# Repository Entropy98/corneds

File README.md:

# Dependencies
 * PyOCD
 * Pico-SDK
 * gdb-multiarch
 * gcc-arm-none-eabi

# Flashing
1. run `./scripts/flash.sh ./build/corneds_<side>.elf` in the firmware directory
2. Enter `target remote localhost:3333` to connect to started gdb server
**cannot connect with gdb-multiarch --pid argument due to ptrace vulnerability in system**

# To Do
## PCB

## Hardware

## Firmware
 * Tests
   * test debug_print test
     * unclear why uart isn't working

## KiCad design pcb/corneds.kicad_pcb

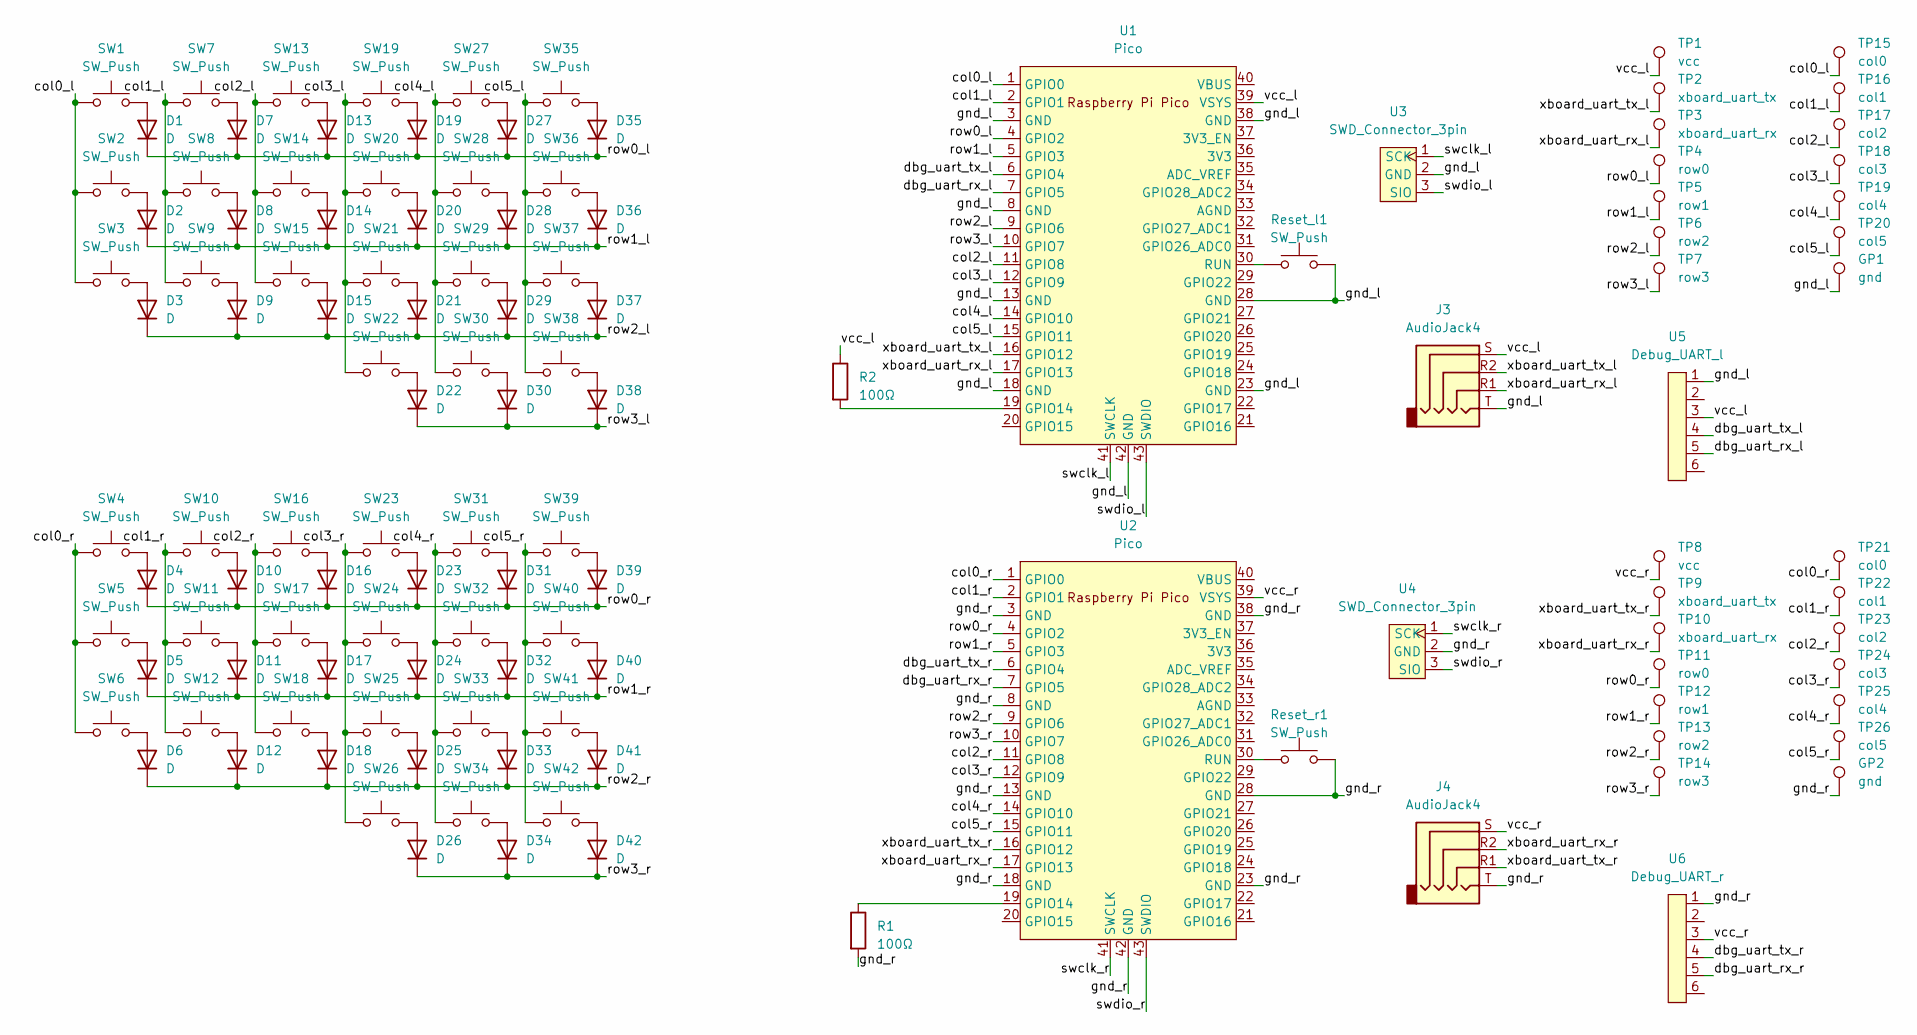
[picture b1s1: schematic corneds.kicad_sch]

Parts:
D1, D2, D3, D4, D5, D6, D7, D8, D9, D10, D11, D12, D13, D14, D15, D16, D17, D18, D19, D20, D21, D22, D23, D24, D25, D26, D27, D28, D29, D30, D31, D32, D33, D34, D35, D36, D37, D38, D39, D40, D41, D42: D; D_1206_3216Metric
GP1, GP2: gnd; PinHeader_1x01_P2.54mm_Vertical
J3, J4: AudioJack4; Jack_3.5mm_boardsource_TRRS_TH
R1, R2: 100Ω; R_0603_1608Metric
Reset_l1: SW_Push; SW_PTS636_SK25F_SMTR
Reset_r1: SW_Push; SW_PTS636_SK25F_SMTR
SW1, SW2, SW3, SW4, SW5, SW6, SW7, SW8, SW9, SW10, SW11, SW12, SW13, SW14, SW15, SW16, SW17, SW18, SW19, SW20, SW21, SW22, SW23, SW24, SW25, SW26, SW27, SW28, SW29, SW30, SW31, SW32, SW33, SW34, SW35, SW36, SW37, SW38, SW39, SW40, SW41, SW42: SW_Push; Kailh_socket_MX
TP1, TP8: vcc; PinHeader_1x01_P2.54mm_Vertical
TP2, TP9: xboard_uart_tx; PinHeader_1x01_P2.54mm_Vertical
TP3, TP10: xboard_uart_rx; PinHeader_1x01_P2.54mm_Vertical
TP4, TP11: row0; PinHeader_1x01_P2.54mm_Vertical
TP5, TP12: row1; PinHeader_1x01_P2.54mm_Vertical
TP6, TP13: row2; PinHeader_1x01_P2.54mm_Vertical
TP7, TP14: row3; PinHeader_1x01_P2.54mm_Vertical
TP15, TP21: col0; PinHeader_1x01_P2.54mm_Vertical
TP16, TP22: col1; PinHeader_1x01_P2.54mm_Vertical
TP17, TP23: col2; PinHeader_1x01_P2.54mm_Vertical
TP18, TP24: col3; PinHeader_1x01_P2.54mm_Vertical
TP19, TP25: col4; PinHeader_1x01_P2.54mm_Vertical
TP20, TP26: col5; PinHeader_1x01_P2.54mm_Vertical
U1, U2: Pico; RPi_Pico_SMD_TH
U3, U4: SWD_Connector_3pin; SM03B-SRSS-TB
U5: Debug_UART_l; Header_6pin
U6: Debug_UART_r; Header_6pin

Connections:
/col0_l: SW1.1, SW2.1, SW3.1, TP15.1, U1.1 (GPIO0)
/col0_r: SW4.1, SW5.1, SW6.1, TP21.1, U2.1 (GPIO0)
/col1_l: SW7.1, SW8.1, SW9.1, TP16.1, U1.2 (GPIO1)
/col1_r: SW10.1, SW11.1, SW12.1, TP22.1, U2.2 (GPIO1)
/col2_l: SW13.1, SW14.1, SW15.1, TP17.1, U1.11 (GPIO8)
/col2_r: SW16.1, SW17.1, SW18.1, TP23.1, U2.11 (GPIO8)
/col3_l: SW19.1, SW20.1, SW21.1, SW22.1, TP18.1, U1.12 (GPIO9)
/col3_r: SW23.1, SW24.1, SW25.1, SW26.1, TP24.1, U2.12 (GPIO9)
/col4_l: SW27.1, SW28.1, SW29.1, SW30.1, TP19.1, U1.14 (GPIO10)
/col4_r: SW31.1, SW32.1, SW33.1, SW34.1, TP25.1, U2.14 (GPIO10)
/col5_l: SW35.1, SW36.1, SW37.1, SW38.1, TP20.1, U1.15 (GPIO11)
/col5_r: SW39.1, SW40.1, SW41.1, SW42.1, TP26.1, U2.15 (GPIO11)
/dbg_uart_rx_l: U1.7 (GPIO5), U5.5
/dbg_uart_rx_r: U2.7 (GPIO5), U6.5
/dbg_uart_tx_l: U1.6 (GPIO4), U5.4
/dbg_uart_tx_r: U2.6 (GPIO4), U6.4
/gnd_l: GP1.1, J3.T, Reset_l1.2, U1.3 (GND), U1.8 (GND), U1.13 (GND), U1.18 (GND), U1.23 (GND), U1.28 (GND), U1.38 (GND), U1.42 (GND), U3.2 (GND), U5.1
/gnd_r: GP2.1, J4.T, R1.2, Reset_r1.2, U2.3 (GND), U2.8 (GND), U2.13 (GND), U2.18 (GND), U2.23 (GND), U2.28 (GND), U2.38 (GND), U2.42 (GND), U4.2 (GND), U6.1
/row0_l: D1.1 (K), D7.1 (K), D13.1 (K), D19.1 (K), D27.1 (K), D35.1 (K), TP4.1, U1.4 (GPIO2)
/row0_r: D4.1 (K), D10.1 (K), D16.1 (K), D23.1 (K), D31.1 (K), D39.1 (K), TP11.1, U2.4 (GPIO2)
/row1_l: D2.1 (K), D8.1 (K), D14.1 (K), D20.1 (K), D28.1 (K), D36.1 (K), TP5.1, U1.5 (GPIO3)
/row1_r: D5.1 (K), D11.1 (K), D17.1 (K), D24.1 (K), D32.1 (K), D40.1 (K), TP12.1, U2.5 (GPIO3)
/row2_l: D3.1 (K), D9.1 (K), D15.1 (K), D21.1 (K), D29.1 (K), D37.1 (K), TP6.1, U1.9 (GPIO6)
/row2_r: D6.1 (K), D12.1 (K), D18.1 (K), D25.1 (K), D33.1 (K), D41.1 (K), TP13.1, U2.9 (GPIO6)
/row3_l: D22.1 (K), D30.1 (K), D38.1 (K), TP7.1, U1.10 (GPIO7)
/row3_r: D26.1 (K), D34.1 (K), D42.1 (K), TP14.1, U2.10 (GPIO7)
/swclk_l: U1.41 (SWCLK), U3.1 (SCK)
/swclk_r: U2.41 (SWCLK), U4.1 (SCK)
/swdio_l: U1.43 (SWDIO), U3.3 (SIO)
/swdio_r: U2.43 (SWDIO), U4.3 (SIO)
/vcc_l: J3.S, R2.1, TP1.1, U1.39 (VSYS), U5.3
/vcc_r: J4.S, TP8.1, U2.39 (VSYS), U6.3
/xboard_uart_rx_l: J3.R1, TP3.1, U1.17 (GPIO13)
/xboard_uart_rx_r: J4.R2, TP10.1, U2.17 (GPIO13)
/xboard_uart_tx_l: J3.R2, TP2.1, U1.16 (GPIO12)
/xboard_uart_tx_r: J4.R1, TP9.1, U2.16 (GPIO12)
unnamed: D1.2 (A), SW1.2
unnamed: D2.2 (A), SW2.2
unnamed: D3.2 (A), SW3.2
unnamed: D4.2 (A), SW4.2
unnamed: D5.2 (A), SW5.2
unnamed: D6.2 (A), SW6.2
unnamed: D7.2 (A), SW7.2
unnamed: D8.2 (A), SW8.2
unnamed: D9.2 (A), SW9.2
unnamed: D10.2 (A), SW10.2
unnamed: D11.2 (A), SW11.2
unnamed: D12.2 (A), SW12.2
unnamed: D13.2 (A), SW13.2
unnamed: D14.2 (A), SW14.2
unnamed: D15.2 (A), SW15.2
unnamed: D16.2 (A), SW16.2
unnamed: D17.2 (A), SW17.2
unnamed: D18.2 (A), SW18.2
unnamed: D19.2 (A), SW19.2
unnamed: D20.2 (A), SW20.2
unnamed: D21.2 (A), SW21.2
unnamed: D22.2 (A), SW22.2
unnamed: D23.2 (A), SW23.2
unnamed: D24.2 (A), SW24.2
unnamed: D25.2 (A), SW25.2
unnamed: D26.2 (A), SW26.2
unnamed: D27.2 (A), SW27.2
unnamed: D28.2 (A), SW28.2
unnamed: D29.2 (A), SW29.2
unnamed: D30.2 (A), SW30.2
unnamed: D31.2 (A), SW31.2
unnamed: D32.2 (A), SW32.2
unnamed: D33.2 (A), SW33.2
unnamed: D34.2 (A), SW34.2
unnamed: D35.2 (A), SW35.2
unnamed: D36.2 (A), SW36.2
unnamed: D37.2 (A), SW37.2
unnamed: D38.2 (A), SW38.2
unnamed: D39.2 (A), SW39.2
unnamed: D40.2 (A), SW40.2
unnamed: D41.2 (A), SW41.2
unnamed: D42.2 (A), SW42.2
unnamed: R2.2, U1.19 (GPIO14)
unnamed: Reset_l1.1, U1.30 (RUN)
unnamed: R1.1, U2.19 (GPIO14)
unnamed: Reset_r1.1, U2.30 (RUN)

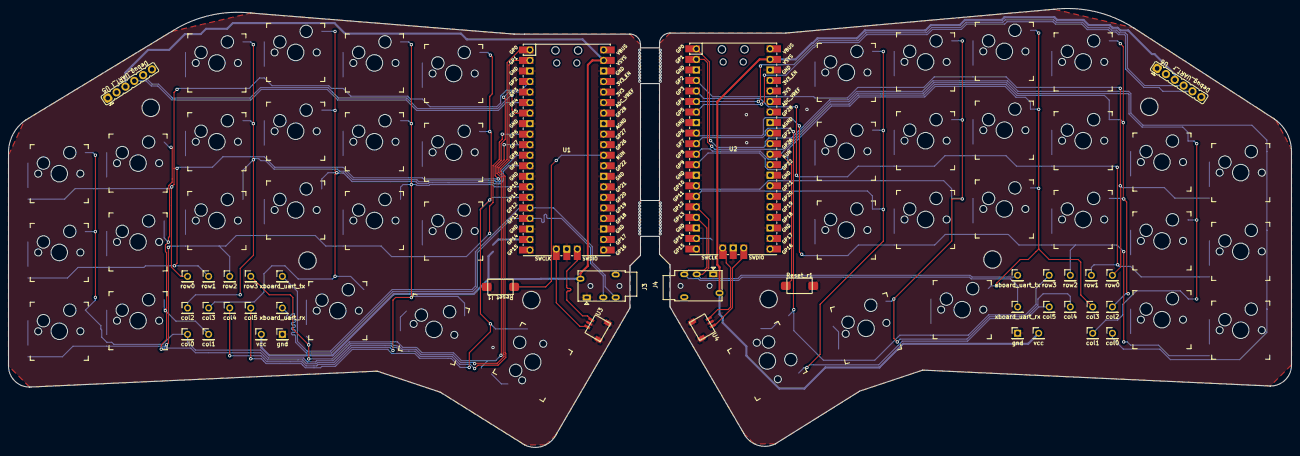
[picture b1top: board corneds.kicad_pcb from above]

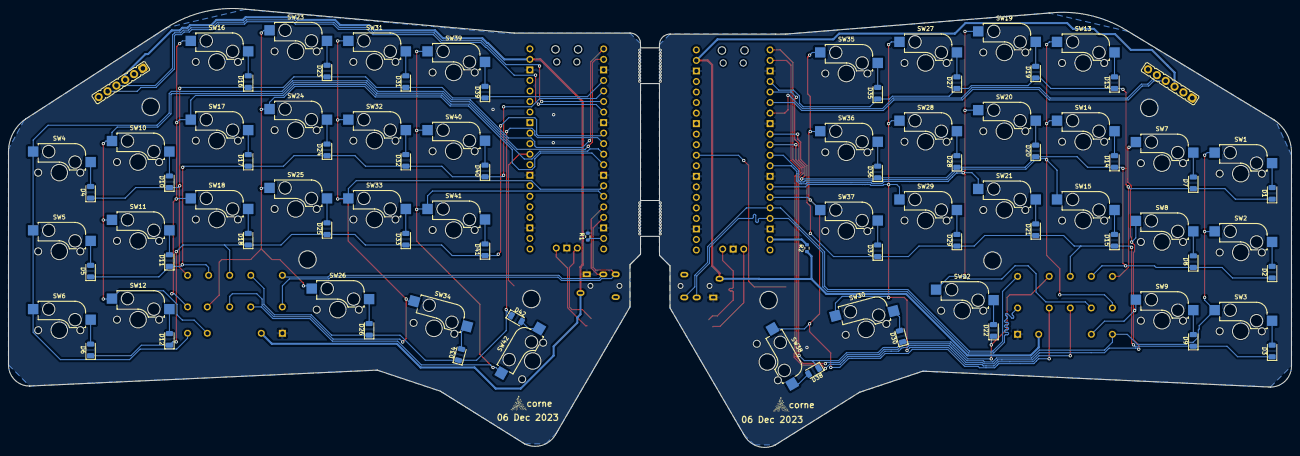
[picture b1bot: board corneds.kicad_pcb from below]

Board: 2 copper layers, 309.4 x 105.8 mm, 126 parts (44 on the bottom side), 82 nets.

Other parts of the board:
mouse-bite-5mm-slot, mouse-bite-5mm-slot#2: VAL**; mouse-bite-5mm-slot

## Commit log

2023-03-03 still working on layout
2023-03-04 no longer committing backups and left side of keyboard almost done placement
2023-03-05 finished left mod key
2023-03-08 finished placing left side
2023-03-09 sch updates
2023-03-10 working on routing
2023-03-23 ordered version
2023-04-15 flattening directory
2023-04-15 sdk is included and cmake is setup
2023-04-15 led blinky works but there are issues with the time slice architecture. Likely in clearing or setting the flags
2023-04-18 fixed timing values
2023-04-19 time slices are time slicing
2023-04-19 sends a bunch of As every second
2023-04-19 made some hopefully unique usb desc
2023-04-19 created todo list
2023-04-19 added some docs I've been using
2023-04-20 updated pcb to kicad 7 and started keymap
2023-04-20 forgot to add keymap
2023-04-21 rp2040 docs and started implementing key circular buffer
2023-04-22 we're not reading any keys
2023-04-22 keys work, macros don't do anything yet, no cross board communication, and preprocessor defines for building different sides aren't working
2023-04-22 it doesn't seem that seperate build folders helps with the sides
2023-04-22 we're building for two
2023-04-23 started on rev2
2023-04-23 fixed trrs jacks and via shapes
2023-04-25 routed left side, placed 3 more mounting holes but want one more
2023-04-25 updated todo
2023-04-26 finished layout on both sides and design front and back plates
2023-04-26 updated date in silk
2023-05-11 usb_detect turns on LED when plugged in but have no tested applying voltage to VBUS directly
2023-05-11 vbus detected is the same for plugged in and supplied vbus otherwise
2023-05-11 made led utils to have better readability over led states and switched board power to VSYS so we can differentiate right from left based on VBUS. This will run the peripheral board at 4.8V instead of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
2023-05-11 updated readme and added protections to scripts against poor usage
2023-05-12 started cross board comms but the uart interrupt isn't occuring on the main board
2023-05-18 dbg_uart and xboard_uart were both uart0 so I swapped dbg_uart with cols 0 and 1
2023-05-18 changed the pins for xboard comms to be the correct ones
2023-05-25 implemented macros, shift keys need work
2023-05-26 implemented shifting but untested
2023-05-27 possibly fixed bug where enter and alt didn't work
2023-05-30 nothing works right now
2023-06-08 was undermasking the shift bit
2023-09-13 added unit test for print Hello World as a keyboard and fixed issue with latching shift but shift still doesn't work as a key
2023-11-11 removed hard coded sides since RevB arrived
2023-11-14 added debug prints
2023-11-15 working on keypress unit test
2023-11-15 added bill of materials
2023-11-15 keypress test passes
2023-11-15 added right and left back for executables until rev3
2023-11-15 test descriptions and fixed shift
2023-11-16 both sides work independently
2023-11-21 left shift isn't working but mod is
2023-11-21 everything seems to be working
2023-11-22 updated to rev3 of the pcb
2023-11-26 added tabs to rev3 and potentially fixed some pin swaps I missed. Also adding alt and gui to key mods
2023-12-04 updating fw for rev3
2023-12-07 right side is working but left side needs pins updated
2023-12-07 fixed silk
2023-12-13 can now send all modifiers at once
2023-12-13 clearing queue on every xboard tx
2023-12-13 everything works but the A key
2023-12-13 needed a sleep when polling cols
2023-12-14 updated front plate and made 3D models to CNC wooden base plate
2023-12-15 finished up hardware
2023-12-15 shrunk mounting holes
2023-12-18 might have had an index out of range bug with the 3rd row
2023-12-18 changed time slices to use pico-sdk us function and pushing key presses on change rather than whenever polled high
2023-12-18 made keypress implementation but might have actually figured out what was wrong
2023-12-18 filling the keycode buffer was the issue
2023-12-19 fixed time slices and tab key. Need to make it so buffer can't add more than one key per transmission
2023-12-20 getting proper keysends from both keyboards but sometimes I might be missing keys on double presses??
2023-12-20 raise and lower were one the wrong sides
2023-12-22 right control sends shift too
2024-01-06 moved hardware and pcb into submodules'
2024-01-06 renamed test binaries
2024-01-08 started interrupt based timing arch
2024-01-10 understanding sdk hardware timers
2024-01-10 gotta test the irq arch now
2024-01-15 trying baremetal timer approach instead of sdk
2024-01-15 hardware timer is working
2024-01-15 working off hardware timers for timing
2024-01-16 timing is far more consistent but xboard comms are broken
2024-01-16 fixed unit tests with timing arch
2024-01-16 updated todo in readme
2024-01-17 xboard comms broke because of USB connected being wrong
2024-01-17 upated readme
2024-01-18 now detecting main kbd based on usb mount status
2024-01-19 latching shift fixed itself
2024-01-19 starting led sm
2024-01-21 writing sm still
2024-01-31 just left alt for spanish keyboard compatibility
2024-02-02 not iterating on itself
2024-02-03 led sm works
2024-02-03 watchdog works
2024-02-06 key cooldowns made general typing worse. A new solution is needed
2024-02-06 keys functions now hold priority on a keypress for 30ms before a key can be another function
2024-02-07 made watchdog task to pet watchdog at highest priority
2024-02-10 periph board now doesn't send alt and gui
2024-05-10 moved the bom the hardware
2025-01-31 modified layout to colemak, updated readme for missing dependencies, and added udev rules
2025-01-31 brought improvements from colemak branch over to develop but not the layout change
2025-11-21 made kbd format configurable
2025-11-21 updated cmakelists and flash script for different probes
